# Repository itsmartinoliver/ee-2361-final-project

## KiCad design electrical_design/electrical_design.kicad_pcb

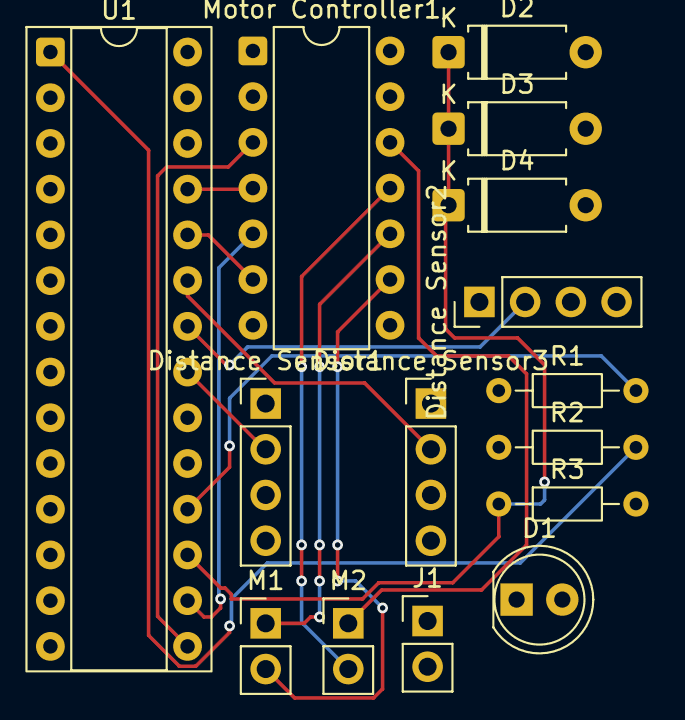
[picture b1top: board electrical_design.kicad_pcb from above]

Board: 2 copper layers, 15 parts (0 on the bottom side), 20 nets.

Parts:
D1: Status LED; LED_D5.0mm
D2, D3, D4: D; D_A-405_P7.62mm_Horizontal
Distance Sensor1, Distance Sensor2, Distance Sensor3: PinHeader_1x04_P2.54mm_Vertical
J1: Conn_01x02_Pin; PinHeader_1x02_P2.54mm_Vertical
M1: Left Motor; PinHeader_1x02_P2.54mm_Vertical
M2: Right Motor; PinHeader_1x02_P2.54mm_Vertical
Motor Controller1: DIP-14_W7.62mm
R1: 1k; R_Axial_DIN0204_L3.6mm_D1.6mm_P7.62mm_Horizontal
R2, R3: 10k; R_Axial_DIN0204_L3.6mm_D1.6mm_P7.62mm_Horizontal
U1: PIC24FJ64GA002-I/SP; DIP-28_W7.62mm_Socket

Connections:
+5V: Distance Sensor1.1 (Vcc), Distance Sensor2.1 (Vcc), Distance Sensor3.1 (Vcc), J1.1, Motor Controller1.2 (VCC), Motor Controller1.7 (MODE), Motor Controller1.13 (VIN), R2.1, U1.13, U1.28
GND: D1.1 (K), Distance Sensor1.4 (Gnd), Distance Sensor2.4 (Gnd), Distance Sensor3.4 (Gnd), J1.2, Motor Controller1.1 (GND), Motor Controller1.14 (GND), R3.2, U1.8, U1.27
unnamed: D1.2 (A), R1.1
unnamed: D2.2 (A), Distance Sensor1.3 (Echo)
unnamed: D2.1 (K), D3.1 (K), D4.1 (K), R3.1, U1.17
unnamed: D3.2 (A), Distance Sensor2.3 (Echo)
unnamed: D4.2 (A), Distance Sensor3.3 (Echo)
unnamed: Distance Sensor1.2 (Trig), U1.21
unnamed: Distance Sensor2.2 (Trig), U1.22
unnamed: Distance Sensor3.2 (Trig), U1.23
unnamed: M1.1 (+), Motor Controller1.10 (AOUT2)
unnamed: M1.2 (-), Motor Controller1.9 (AOUT1)
unnamed: M2.1 (+), Motor Controller1.12 (BOUT2)
unnamed: M2.2 (-), Motor Controller1.11 (BOUT1)
unnamed: Motor Controller1.5 (AENBL), U1.16
unnamed: Motor Controller1.6 (APHASE), U1.24
unnamed: Motor Controller1.3 (BENBL), U1.15
unnamed: Motor Controller1.4 (BPHASE), U1.25
unnamed: R1.2, U1.18
unnamed: R2.2, U1.1

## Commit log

2026-03-29 all files
2026-03-31 KiCAD electrical and boilerplate code
2026-03-31 Simple motor function
2026-03-31 Motor test and distance sensor triggers
2026-03-31 Slower test for motors
2026-04-01 Updated electrical and input capture for sensors
2026-04-01 Pull-down resistor on ECHO input and bug fixes
2026-04-03 Distance sensor fixes
2026-04-04 New distance sensor fix
2026-04-04 KiCAD Footprints
2026-04-23 Working corrective actions
2026-04-25 Status LED to indicate program restart
2026-04-26 fix: Some editor specific configs and a proper gitignore
    squashdown commit add gitignore also
2026-04-26 remove build/dist directory & private nbproject files from git tracking
    remove dist from git tracking
    remove nbproject from git tracking
2026-04-26 remove more generated files
2026-04-26 add build system
2026-04-26 wip commit
2026-04-26 Add files via upload
    General framework for a function based version of the maze solver.
    To add: major moving forward function or logic, adjusting timer values and counts for proper movement, all of PID implementation, sensor updating may not work (I'm not sure), break out into libraries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
2026-04-27 gwip
